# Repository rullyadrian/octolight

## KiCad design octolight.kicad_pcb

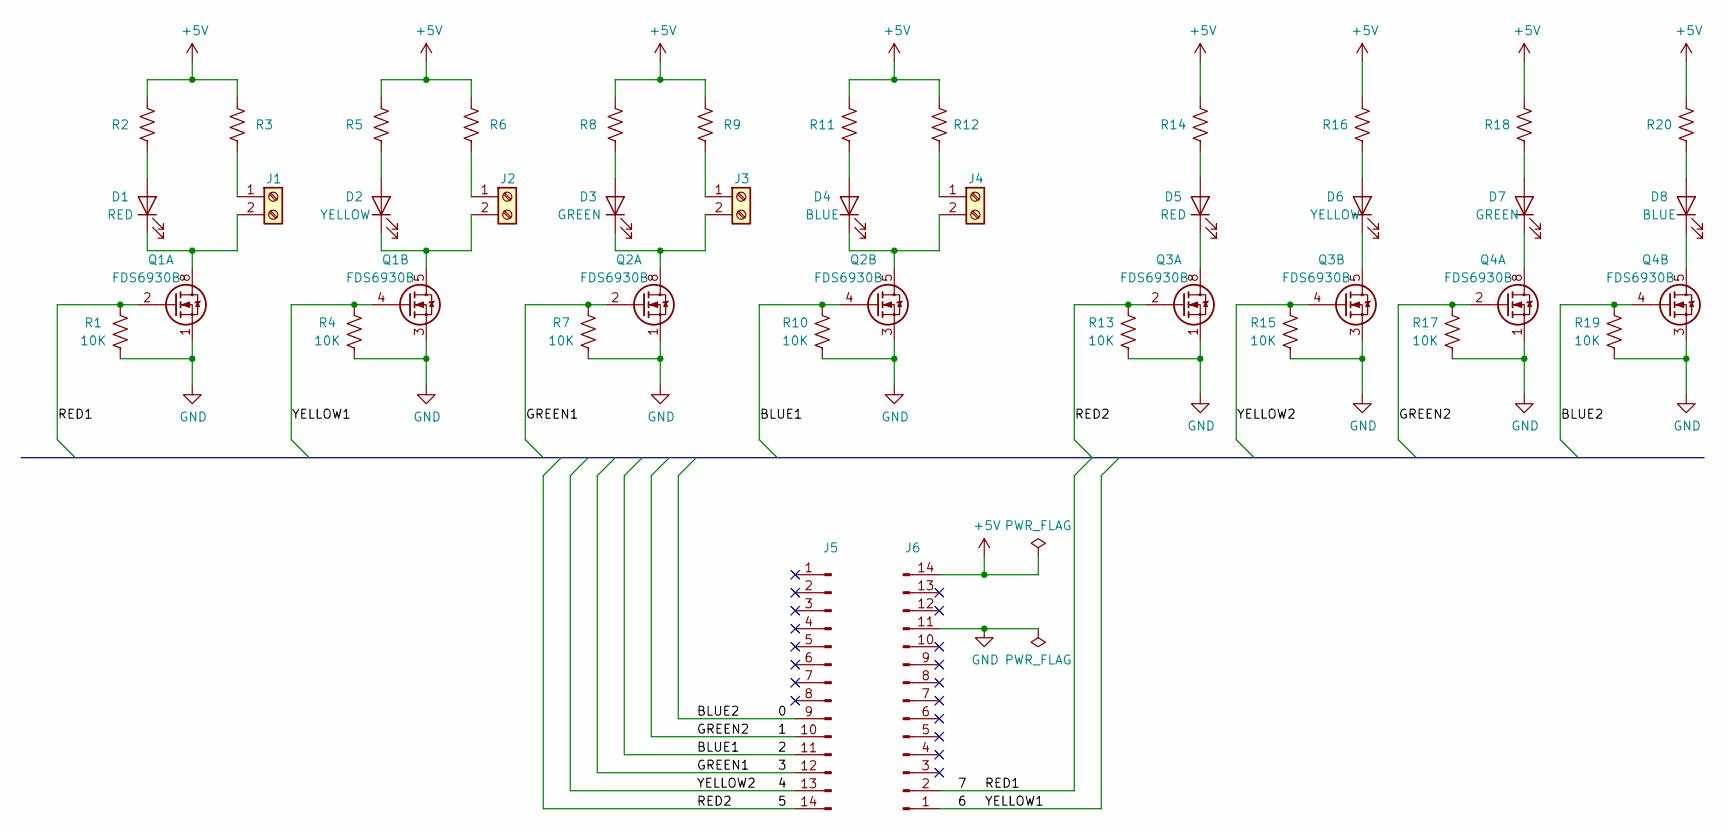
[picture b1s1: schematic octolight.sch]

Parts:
D1, D5: RED; LED_0805_2012Metric_Pad1.15x1.40mm_HandSolder
D2, D6: YELLOW; LED_0805_2012Metric_Pad1.15x1.40mm_HandSolder
D3, D7: GREEN; LED_0805_2012Metric_Pad1.15x1.40mm_HandSolder
D4, D8: BLUE; LED_0805_2012Metric_Pad1.15x1.40mm_HandSolder
J1, J2, J3, J4: Screw_Terminal_01x02; TerminalBlock_TE_282834-2_1x02_P2.54mm_Horizontal
J5, J6: Conn_01x14_Male; PinHeader_1x14_P2.54mm_Vertical
Q1, Q2, Q3, Q4: FDS6930B; SOIC-8_3.9x4.9mm_P1.27mm
R1, R4, R7, R10, R13, R15, R17, R19: 10K; R_0805_2012Metric_Pad1.15x1.40mm_HandSolder
R2, R3, R5, R6, R8, R9, R11, R12, R14, R16, R18, R20: R_US; R_0805_2012Metric_Pad1.15x1.40mm_HandSolder

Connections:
+5V: J6.14, R2.2, R3.2, R5.2, R6.2, R8.2, R9.2, R11.2, R12.2, R14.2, R16.2, R18.2, R20.2
/0: J5.9, Q4.4 (G2), R19.2
/1: J5.10, Q4.2 (G1), R17.2
/2: J5.11, Q2.4 (G2), R10.2
/3: J5.12, Q2.2 (G1), R7.2
/4: J5.13, Q3.4 (G2), R15.2
/5: J5.14, Q3.2 (G1), R13.2
/6: J6.1, Q1.4 (G2), R4.2
/7: J6.2, Q1.2 (G1), R1.2
GND: J6.11, Q1.1 (S1), Q1.3 (S2), Q2.1 (S1), Q2.3 (S2), Q3.1 (S1), Q3.3 (S2), Q4.1 (S1), Q4.3 (S2), R1.1, R4.1, R7.1, R10.1, R13.1, R15.1, R17.1, R19.1
unnamed: D1.1 (K), J1.2, Q1.7 (D1), Q1.8 (D1)
unnamed: D1.2 (A), R2.1
unnamed: D2.1 (K), J2.2, Q1.5 (D2), Q1.6 (D2)
unnamed: D2.2 (A), R5.1
unnamed: D3.1 (K), J3.2, Q2.7 (D1), Q2.8 (D1)
unnamed: D3.2 (A), R8.1
unnamed: D4.1 (K), J4.2, Q2.5 (D2), Q2.6 (D2)
unnamed: D4.2 (A), R11.1
unnamed: D5.1 (K), Q3.7 (D1), Q3.8 (D1)
unnamed: D5.2 (A), R14.1
unnamed: D6.1 (K), Q3.5 (D2), Q3.6 (D2)
unnamed: D6.2 (A), R16.1
unnamed: D7.1 (K), Q4.7 (D1), Q4.8 (D1)
unnamed: D7.2 (A), R18.1
unnamed: D8.1 (K), Q4.5 (D2), Q4.6 (D2)
unnamed: D8.2 (A), R20.1
unnamed: J1.1, R3.1
unnamed: J2.1, R6.1
unnamed: J3.1, R9.1
unnamed: J4.1, R12.1

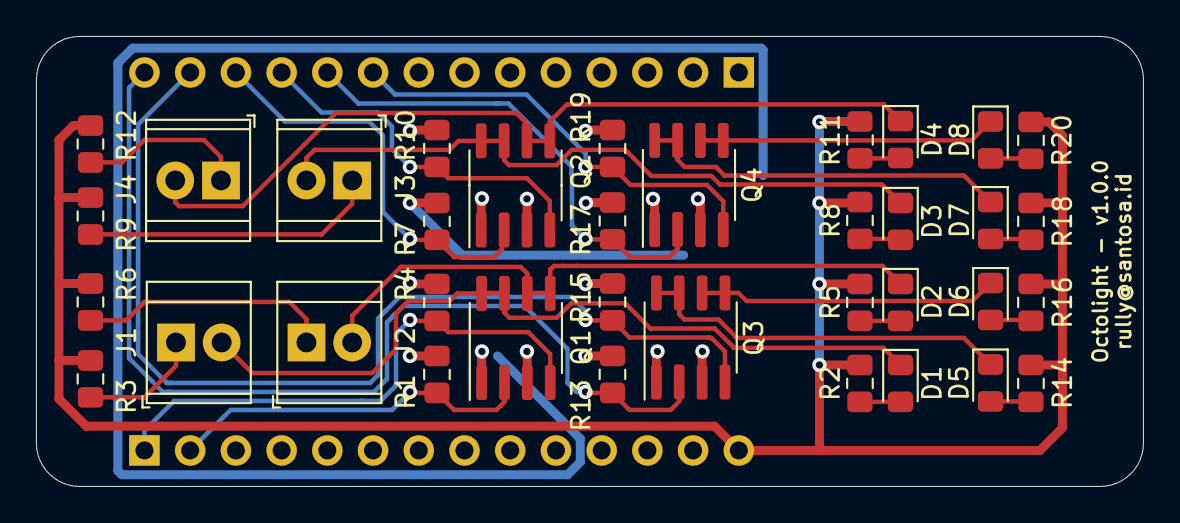
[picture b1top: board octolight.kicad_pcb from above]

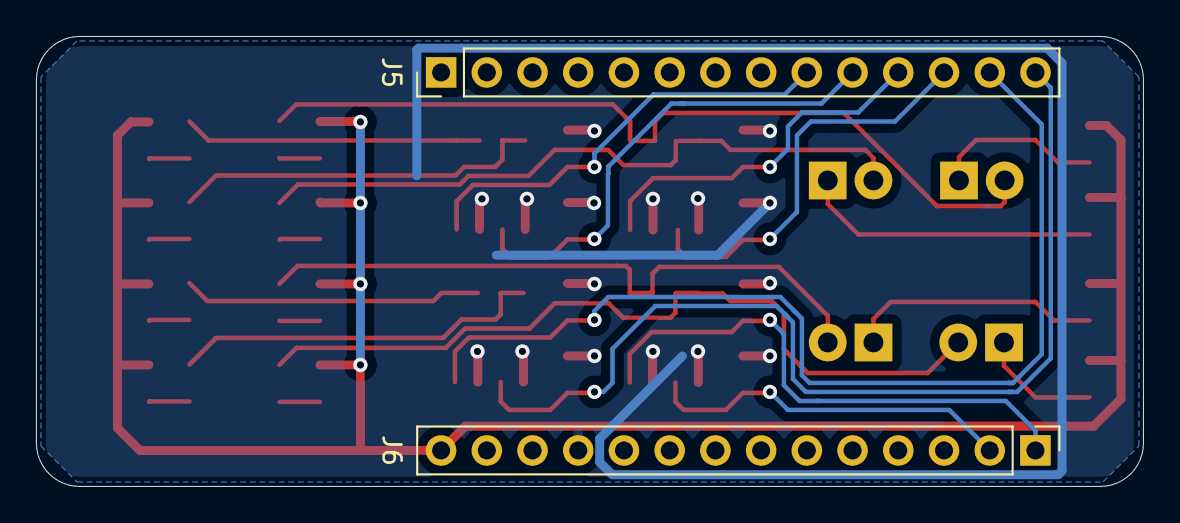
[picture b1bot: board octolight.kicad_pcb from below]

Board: 2 copper layers, 61.5 x 25.0 mm, 38 parts (2 on the bottom side), 30 nets.

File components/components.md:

# Components

| Reference                           | Description                                                                                         | Manufacturer               | Part No          | Remark                        |
|-------------------------------------|-----------------------------------------------------------------------------------------------------|----------------------------|------------------|-------------------------------|
| D1, D5                              | LED, Red, SMD, 0805, 2 mA, 1.75 V, 630 nm                                                           | KINGBRIGHT                 | KPTD-2012LVSURCK |                               |
| D2, D6                              | LED, Yellow, SMD, 0805, 2 mA, 1.85 V, 590 nm                                                        | KINGBRIGHT                 | KPTD-2012LVSYCK  |                               |
| D3, D7                              | LED, Green, SMD, 0805, 2 mA, 2.65 V, 525 nm                                                         | KINGBRIGHT                 | KPTD-2012LVZGCK  |                               |
| D4, D8                              | LED, Blue, SMD, 0805, 2 mA, 2.65 V, 465 nm                                                          | KINGBRIGHT                 | KPTD-2012LVQBC-D |                               |
| R3, R6, R9, R12                     | SMD Chip Resistor, 0805 [2012 Metric], 82 ohm, MCWR Series, 150 V, Thick Film, 125 mW               | MULTICOMP PRO              | MCWR08X82R0FTL   | With 2.60 V, 30 mA LED string |
| R3, R6, R9, R12                     | SMD Chip Resistor, 0805 [2012 Metric], 150 ohm, MCWR Series, 150 V, Thick Film, 125 mW              | MULTICOMP PRO              | MCWR08X1500FTL   | With 2.60 V, 15 mA LED string |
| R8, R11, R18, R20                   | SMD Chip Resistor, 0805 [2012 Metric], 1.2 kohm, MCWR Series, 150 V, Thick Film, 125 mW             | MULTICOMP PRO              | MCWR08X1201FTL   |                               |
| R2, R5, R14, R16                    | SMD Chip Resistor, 0805 [2012 Metric], 1.6 kohm, MCWR Series, 150 V, Thick Film, 125 mW             | MULTICOMP PRO              | MCWR08X1601FTL   |                               |
| R1, R4, R7, R10, R13, R15, R17, R19 | SMD Chip Resistor, 0805 [2012 Metric], 10 kohm, MCWR Series, 150 V, Thick Film, 125 mW              | MULTICOMP PRO              | MCWR08X1002FTL   |                               |
| Q1, Q2, Q3, Q4                      | Dual MOSFET, Dual N Channel, 5.5 A, 30 V, 0.031 ohm, 10 V, 1.9 V                                    | ON SEMICONDUCTOR           | FDS6930B         |                               |
| J1, J2, J3, J4                      | Wire-To-Board Terminal Block, 2.54 mm, 2 Ways, 30 AWG, 16 AWG, 1.4 mm², Screw                       | TE CONNECTIVITY / BUCHANAN | 282834-2         |                               |
| J5, J6                              | Board-To-Board Connector, Vertical, 2.54 mm, 14 Contacts, Header, MC34 Series, Through Hole, 1 Rows | MULTICOMP                  | MC34735          |                               |

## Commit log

2019-12-01 Add drawing of Arduino MKR board
2019-12-01 Add KiCad project
2019-12-01 Add generated Gerber files
2019-12-01 Add .gitignore
2019-12-15 Add list of components
2019-12-19 Add .vscode to .gitignore
2019-12-19 Add sketch: glow
2019-12-19 Add sketch: sequential
2019-12-19 Update sketch sequential with glow
2019-12-19 Add scaling factor to control brightness
2019-12-23 Add sketch: sequential2
